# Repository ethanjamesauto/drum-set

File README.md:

## Project Overview
This project aims to produce an electronic drum set that is silent yet feels nearly identical to a real acoustic drum set. I've split the project into two phases:
* Phase 1 - creating a basic kit with a kick drum trigger and 2 drum pads as a proof-of-concept **(completed)**
* Phase 2 - creating a full drum kit with kick trigger, 4 drum pads, and 4 electronic cymbals **(in progress)**

## Full Outline

### Drum Module
* I'm currently using an ESP32 with [edrumulus](https://github.com/corrados/edrumulus/tree/main) and a custom-built analog frontend
  * The ESP32 has a drawback of not being a native MIDI device - it requires a script to appear as a virtual MIDI device
  * I'll be replacing it with a teensy 4.2, which solves this issue. Additionally, it has an SD card slot and plenty of processing power, so hopefully I'll be able to use it as a standalone synthesizer.
* I'm currently designing a PCB which includes the teensy, 8 input jacks, analog frontends for each channel, and display/keypad for controlling settings

Materials:
* Teensy 4.2
* 8x 1/4 inch PCB mount TRS audio jacks
* 16x2 character LCD
* Arduino numeric keypad
* 8x TRS audio cable

Features:
* Teensy 4.2 based - with headers for all GPIOs
* headers for piezo inputs (test points)
* i2c headers for display (VCC, GND, SDA, SCL)
* 8 gpios for numeric keypad

### Drum Pads
Materials:
  * Drum Shells
  * Drum top/bottom
  * M6x50mm bolts / M6 wing nuts (2x8 + 2x10 = 36 total)
  * Regular M6 nuts for attaching drum mount
  * M3x10mm bolts/nuts (already own)
  * 2x10in drum head, 2x12in drum head
  * piezos/trigger cones/audio jacks

Notes:
* All drum shells will be printed with [shell.scad](shell.scad) (my script for generating drum shells)
* Drum design is from [Open E-Drums](https://open-e-drums.com/hardware/download_pad_noshell.html)

### Hi-Hat
* Will likely use this [optical hi-hat controller](https://open-e-drums.com/hardware/download_hhc.html)

### Mounting Hardware
Rack will likely be a second-hand alesis e-drum rack

TODO:
* modify pcb to allow for optical hi hat sensor

Tom mounts:
*  [Alesis drum clamp mount](https://www.printables.com/model/244788-alesis-electronic-drum-clamp-mount) - these each require an Alesis L-rod
* Modify this [Roland mount](https://open-e-drums.com/hardware/download_mount.html) to change the hole from 11mm (Roland) to 9mm (Alesis)

Snare mount:
* ???

Cymbal Mounts:
* These could use the same alesis drum clamp mounts, but they require a cymbal mount instead of an L-rod (much more expensive)

Hi-Hat Mount:
* Real hi-hat stand. It's really not worth bothering with anything else.

## Members
Ethan James, Computer Engineering Student (2024) -
ethanjamesauto@vt.edu

## Images
Drum module PCB:

This is the prototype (Phase 1):

## Drum pad notes
* height from base plate is 47.5mm
* Trigger cones are 35mm tall
* Recommended height of trigger cone above shell is maybe 1.5mm or 1/16in
* definitely use spacers (3d printed or some other plastic) to adjust height of plate

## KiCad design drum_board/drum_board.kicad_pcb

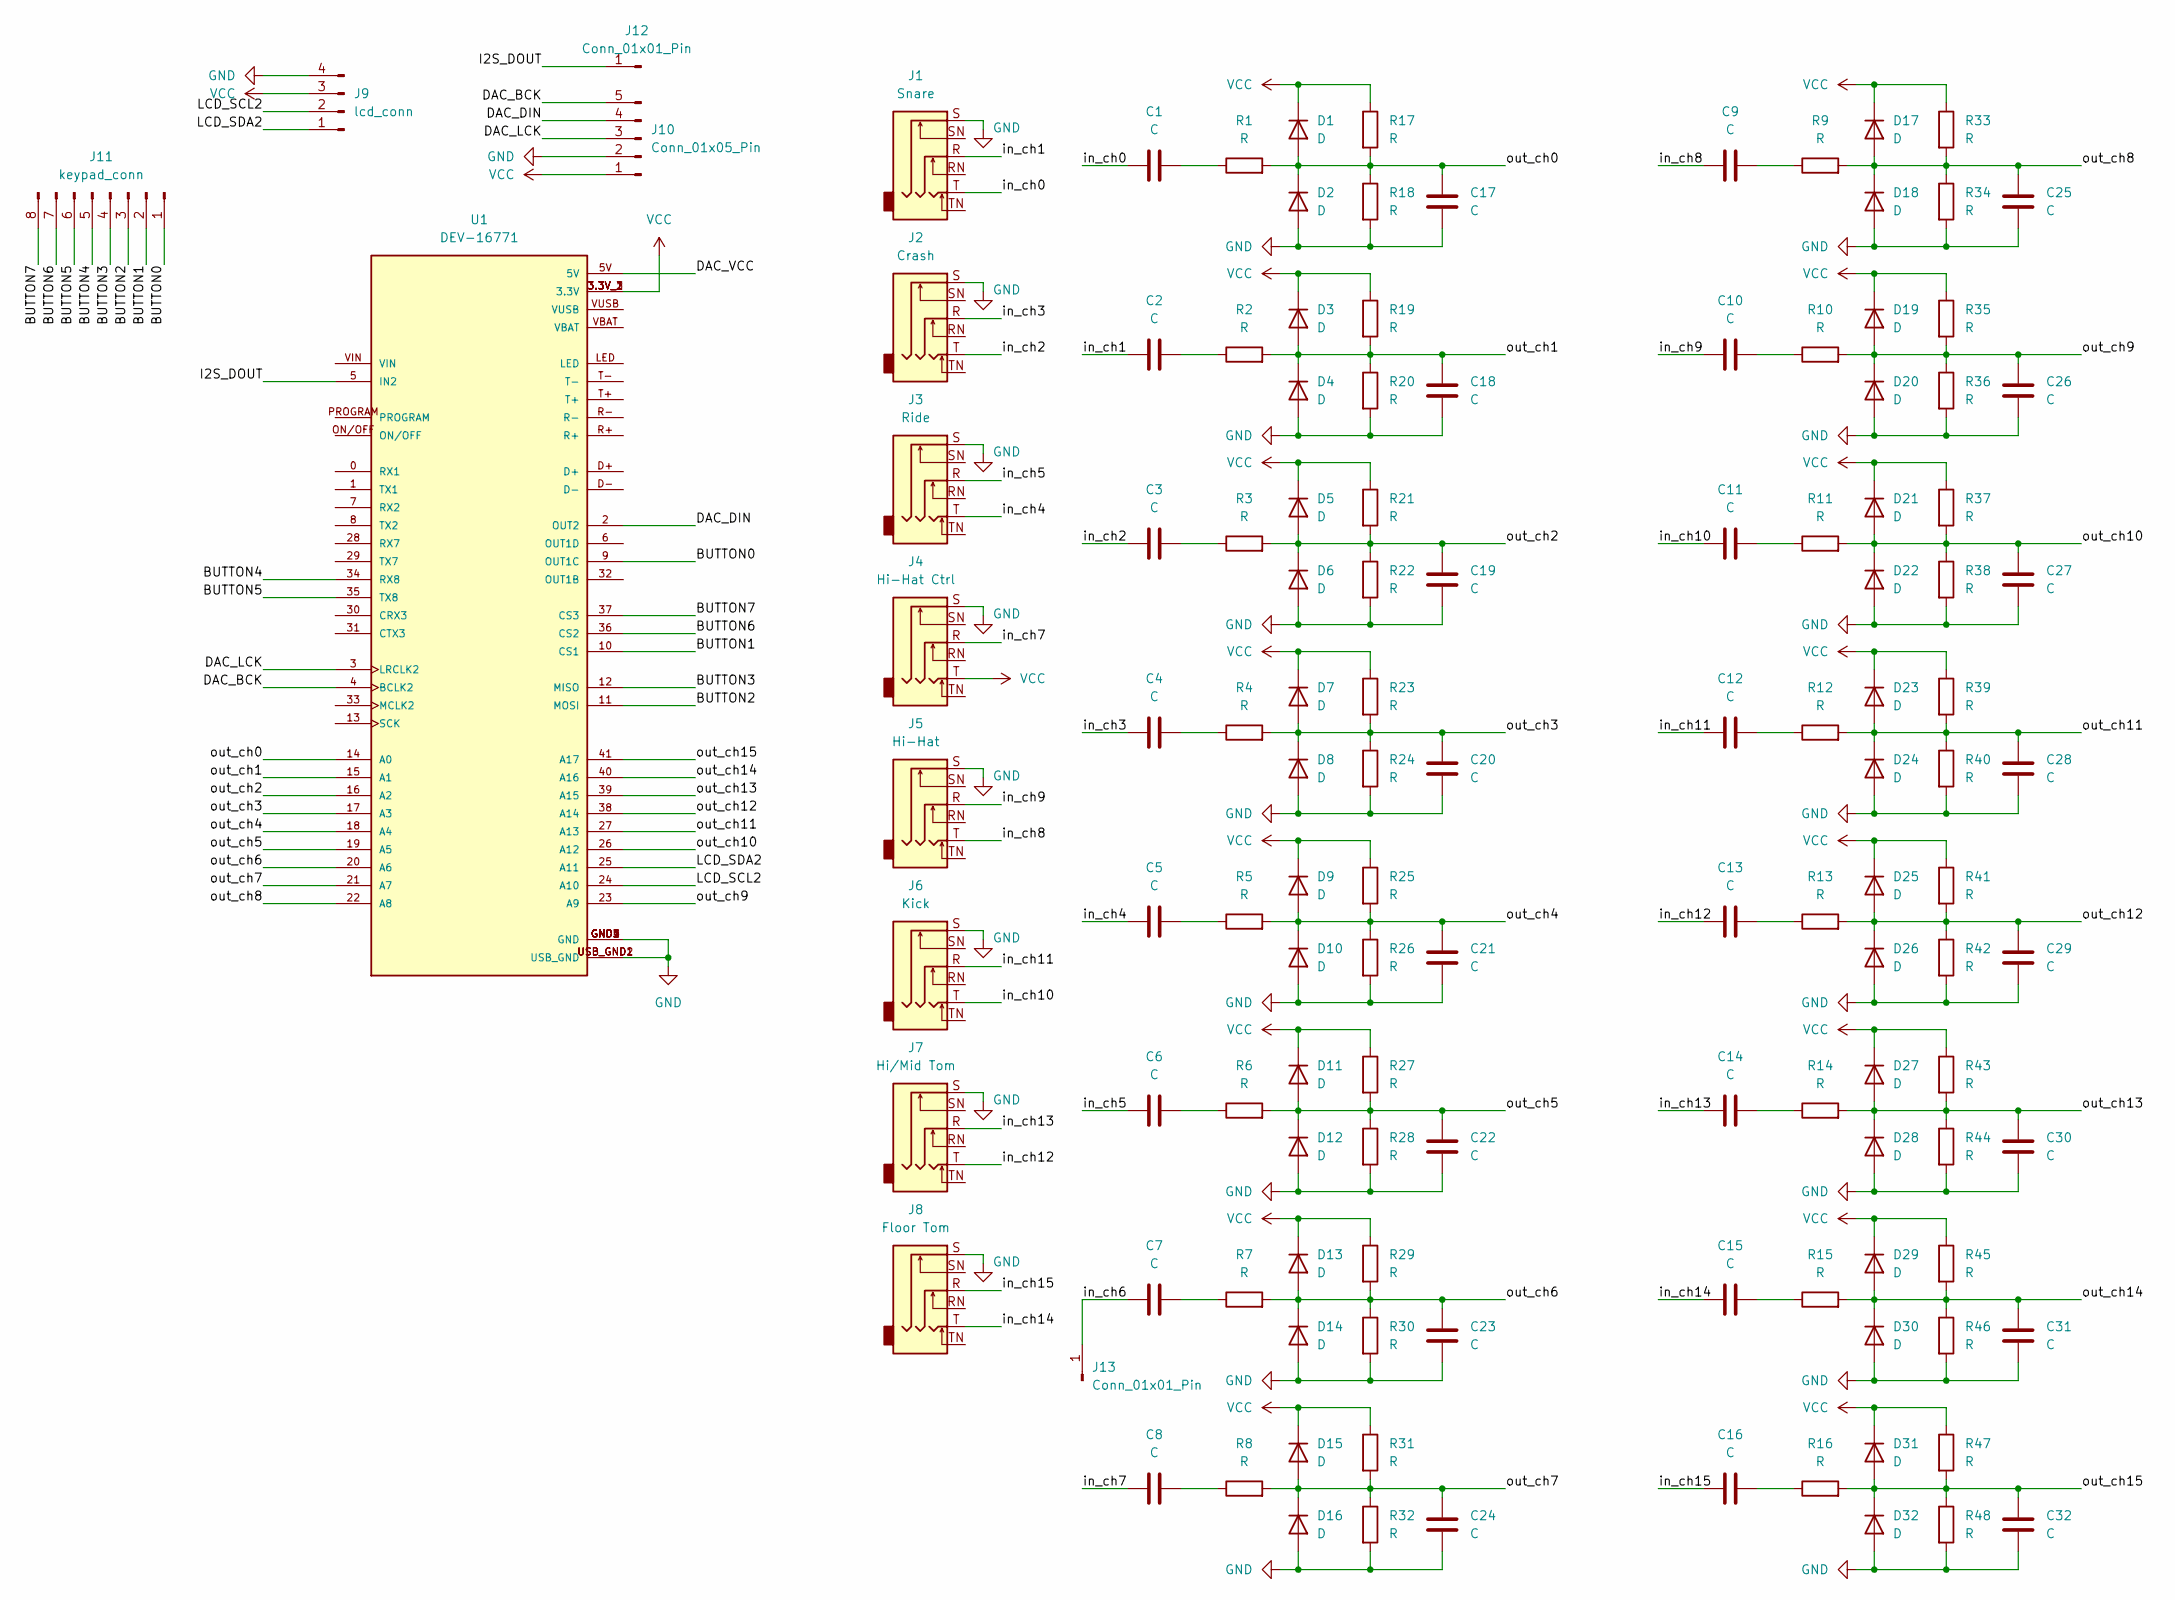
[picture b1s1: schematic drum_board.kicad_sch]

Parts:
C1, C2, C3, C4, C5, C6, C7, C8, C9, C10, C11, C12, C13, C14, C15, C16, C17, C18, C19, C20, C21, C22, C23, C24, C25, C26, C27, C28, C29, C30, C31, C32: C; C_Disc_D5.0mm_W2.5mm_P5.00mm
D1, D2, D3, D4, D5, D6, D7, D8, D9, D10, D11, D12, D13, D14, D15, D16, D17, D18, D19, D20, D21, D22, D23, D24, D25, D26, D27, D28, D29, D30, D31, D32: D; D_DO-35_SOD27_P7.62mm_Horizontal
J1: Snare; Jack_6.35mm_Neutrik_NMJ6HCD2_Horizontal
J2: Crash; Jack_6.35mm_Neutrik_NMJ6HCD2_Horizontal
J3: Ride; Jack_6.35mm_Neutrik_NMJ6HCD2_Horizontal
J4: Hi-Hat Ctrl; Jack_6.35mm_Neutrik_NMJ6HCD2_Horizontal
J5: Hi-Hat; Jack_6.35mm_Neutrik_NMJ6HCD2_Horizontal
J6: Kick; Jack_6.35mm_Neutrik_NMJ6HCD2_Horizontal
J7: Hi/Mid Tom; Jack_6.35mm_Neutrik_NMJ6HCD2_Horizontal
J8: Floor Tom; Jack_6.35mm_Neutrik_NMJ6HCD2_Horizontal
J9: lcd_conn; PinHeader_1x04_P2.54mm_Vertical
J10: Conn_01x05_Pin; PinHeader_1x05_P2.54mm_Vertical
J11: keypad_conn; PinHeader_1x08_P2.54mm_Vertical
J12, J13: Conn_01x01_Pin; PinHeader_1x01_P2.54mm_Vertical
R1, R2, R3, R4, R5, R6, R7, R8, R9, R10, R11, R12, R13, R14, R15, R16, R17, R18, R19, R20, R21, R22, R23, R24, R25, R26, R27, R28, R29, R30, R31, R32, R33, R34, R35, R36, R37, R38, R39, R40, R41, R42, R43, R44, R45, R46, R47, R48: R; R_Axial_DIN0207_L6.3mm_D2.5mm_P10.16mm_Horizontal
U1: DEV-16771; MODULE_DEV-16771; PARTREV 4.1

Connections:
/BUTTON0: J11.1, U1.9 (OUT1C)
/BUTTON1: J11.2, U1.10 (CS1)
/BUTTON2: J11.3, U1.11 (MOSI)
/BUTTON3: J11.4, U1.12 (MISO)
/BUTTON4: J11.5, U1.34 (RX8)
/BUTTON5: J11.6, U1.35 (TX8)
/BUTTON6: J11.7, U1.36 (CS2)
/BUTTON7: J11.8, U1.37 (CS3)
/DAC_BCK: J10.5, U1.4 (BCLK2)
/DAC_DIN: J10.4, U1.2 (OUT2)
/DAC_LCK: J10.3, U1.3 (LRCLK2)
/DAC_VCC: U1.5V
/I2S_DOUT: J12.1, U1.5 (IN2)
/LCD_SCL2: J9.2, U1.24 (A10)
/LCD_SDA2: J9.1, U1.25 (A11)
/in_ch0: C1.1, J1.T
/in_ch1: C2.1, J1.R
/in_ch2: C3.1, J2.T
/in_ch3: C4.1, J2.R
/in_ch4: C5.1, J3.T
/in_ch5: C6.1, J3.R
/in_ch6: C7.1, J13.1
/in_ch7: C8.1, J4.R
/in_ch8: C9.1, J5.T
/in_ch9: C10.1, J5.R
/in_ch10: C11.1, J6.T
/in_ch11: C12.1, J6.R
/in_ch12: C13.1, J7.T
/in_ch13: C14.1, J7.R
/in_ch14: C15.1, J8.T
/in_ch15: C16.1, J8.R
/out_ch0: C17.2, D1.2 (A), D2.1 (K), R1.2, R17.2, R18.1, U1.14 (A0)
/out_ch1: C18.2, D3.2 (A), D4.1 (K), R2.2, R19.2, R20.1, U1.15 (A1)
/out_ch2: C19.2, D5.2 (A), D6.1 (K), R3.2, R21.2, R22.1, U1.16 (A2)
/out_ch3: C20.2, D7.2 (A), D8.1 (K), R4.2, R23.2, R24.1, U1.17 (A3)
/out_ch4: C21.2, D9.2 (A), D10.1 (K), R5.2, R25.2, R26.1, U1.18 (A4)
/out_ch5: C22.2, D11.2 (A), D12.1 (K), R6.2, R27.2, R28.1, U1.19 (A5)
/out_ch6: C23.2, D13.2 (A), D14.1 (K), R7.2, R29.2, R30.1, U1.20 (A6)
/out_ch7: C24.2, D15.2 (A), D16.1 (K), R8.2, R31.2, R32.1, U1.21 (A7)
/out_ch8: C25.2, D17.2 (A), D18.1 (K), R9.2, R33.2, R34.1, U1.22 (A8)
/out_ch9: C26.2, D19.2 (A), D20.1 (K), R10.2, R35.2, R36.1, U1.23 (A9)
/out_ch10: C27.2, D21.2 (A), D22.1 (K), R11.2, R37.2, R38.1, U1.26 (A12)
/out_ch11: C28.2, D23.2 (A), D24.1 (K), R12.2, R39.2, R40.1, U1.27 (A13)
/out_ch12: C29.2, D25.2 (A), D26.1 (K), R13.2, R41.2, R42.1, U1.38 (A14)
/out_ch13: C30.2, D27.2 (A), D28.1 (K), R14.2, R43.2, R44.1, U1.39 (A15)
/out_ch14: C31.2, D29.2 (A), D30.1 (K), R15.2, R45.2, R46.1, U1.40 (A16)
/out_ch15: C32.2, D31.2 (A), D32.1 (K), R16.2, R47.2, R48.1, U1.41 (A17)
GND: C17.1, C18.1, C19.1, C20.1, C21.1, C22.1, C23.1, C24.1, C25.1, C26.1, C27.1, C28.1, C29.1, C30.1, C31.1, C32.1, D2.2 (A), D4.2 (A), D6.2 (A), D8.2 (A), D10.2 (A), D12.2 (A), D14.2 (A), D16.2 (A), D18.2 (A), D20.2 (A), D22.2 (A), D24.2 (A), D26.2 (A), D28.2 (A), D30.2 (A), D32.2 (A), J1.S, J2.S, J3.S, J4.S, J5.S, J6.S, J7.S, J8.S, J9.4, J10.2, R18.2, R20.2, R22.2, R24.2, R26.2, R28.2, R30.2, R32.2, R34.2, R36.2, R38.2, R40.2, R42.2, R44.2, R46.2, R48.2, U1.GND1 (GND), U1.GND2 (GND), U1.GND3 (GND), U1.GND4 (GND), U1.GND5 (GND), U1.USB_GND1 (USB_GND), U1.USB_GND2 (USB_GND)
unnamed: C1.2, R1.1
unnamed: C2.2, R2.1
unnamed: C3.2, R3.1
unnamed: C4.2, R4.1
unnamed: C5.2, R5.1
unnamed: C6.2, R6.1
unnamed: C7.2, R7.1
unnamed: C8.2, R8.1
unnamed: C9.2, R9.1
unnamed: C10.2, R10.1
unnamed: C11.2, R11.1
unnamed: C12.2, R12.1
unnamed: C13.2, R13.1
unnamed: C14.2, R14.1
unnamed: C15.2, R15.1
unnamed: C16.2, R16.1
VCC: D1.1 (K), D3.1 (K), D5.1 (K), D7.1 (K), D9.1 (K), D11.1 (K), D13.1 (K), D15.1 (K), D17.1 (K), D19.1 (K), D21.1 (K), D23.1 (K), D25.1 (K), D27.1 (K), D29.1 (K), D31.1 (K), J4.T, J9.3, J10.1, R17.1, R19.1, R21.1, R23.1, R25.1, R27.1, R29.1, R31.1, R33.1, R35.1, R37.1, R39.1, R41.1, R43.1, R45.1, R47.1, U1.3.3V_1 (3.3V), U1.3.3V_2 (3.3V), U1.3.3V_3 (3.3V)

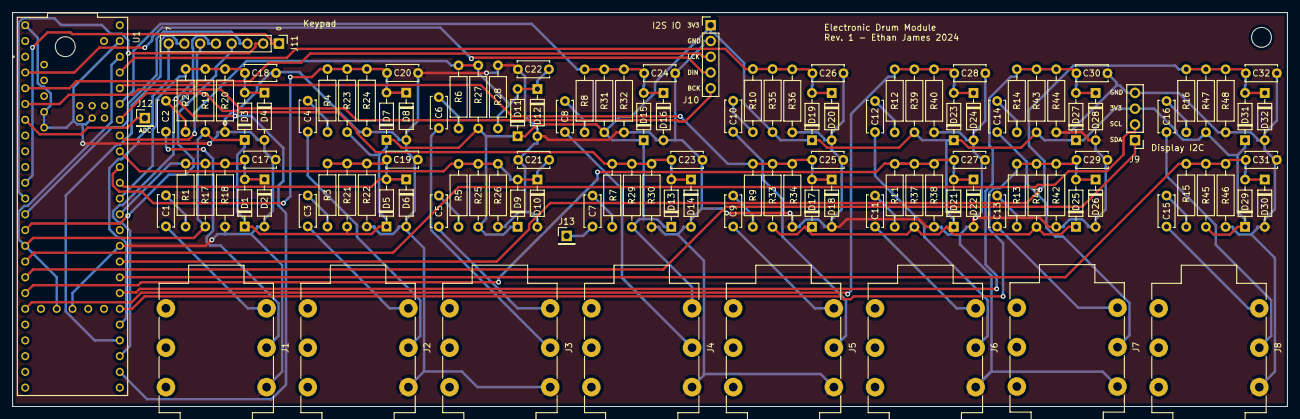
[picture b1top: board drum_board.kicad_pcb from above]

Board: 2 copper layers, 205.4 x 63.5 mm, 126 parts (0 on the bottom side), 64 nets.

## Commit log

2024-09-13 Add project files and update README
2024-10-17 Add new alesis drum coupler
2024-10-17 Update shell design
2024-10-19 Add files
2024-10-20 Add submodules
2024-10-20 Add untracked files
2024-10-22 Fix bad alesis mount dimensions
2024-10-28 Add hi hat sensor model
